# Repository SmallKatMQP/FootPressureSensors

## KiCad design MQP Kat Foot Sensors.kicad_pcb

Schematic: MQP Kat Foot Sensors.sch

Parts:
C3, C4, C5, C6, C7, C8, C9, C10, C11, C12, C13, C14, C15, C16: 100NF; C_0402_1005Metric
C17, C18: C; C_0402_1005Metric
IC1, IC2, IC3, IC4, IC5, IC6, IC7: BMP280; 8-PIN-METAL-LID-LGA_1; Manufacturer_Part_Number BMP280
J1: Conn_01x06_Male; Molex_CLIK-Mate_502443-0670_1x06-1MP_P2.00mm_Vertical
J2, J3: Conn_01x04_Male; 1x4Pads
R1: 100K; R_0402_1005Metric
U1: STM32L432KBUx; QFN-32-1EP_5x5mm_P0.5mm_EP3.45x3.45mm
U2: MIC5501-3.0YM5; SOT-23-5

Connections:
+3V3: C3.2, C4.1, C5.2, C6.1, C7.2, C8.1, C9.2, C10.1, C11.2, C12.1, C13.2, C14.1, C15.2, C16.1, C18.2, IC1.6, IC1.8, IC2.6, IC2.8, IC3.6, IC3.8, IC4.6, IC4.8, IC5.6, IC5.8, IC6.6, IC6.8, IC7.6, IC7.8, J2.4, J3.4, U1.1, U1.5, U1.17, U2.5 (VOUT)
+BATT: C17.2, J1.6, U2.1 (VIN), U2.3 (EN)
CS: J1.1, U1.14
CS1: IC1.2, U1.6
CS2: IC4.2, U1.15
CS3: IC2.2, U1.25
CS4: IC5.2, U1.20
CS5: IC7.2, U1.18
CS6: IC3.2, U1.10
CS7: IC6.2, U1.9
GND: C3.1, C4.2, C5.1, C6.2, C7.1, C8.2, C9.1, C10.2, C11.1, C12.2, C13.1, C14.2, C15.1, C16.2, C17.1, C18.1, IC1.1, IC1.7, IC2.1, IC2.7, IC3.1, IC3.7, IC4.1, IC4.7, IC5.1, IC5.7, IC6.1, IC6.7, IC7.1, IC7.7, J1.5, J2.3, J3.3, R1.2, U1.16, U1.32, U1.33, U2.2 (GND)
MISO: IC3.5, IC4.5, IC6.5, IC7.5, J1.3, U1.12
MISO2: IC1.5, IC2.5, IC5.5, U1.27
MOSI: IC3.3, IC4.3, IC6.3, IC7.3, J1.2, U1.13
MOSI2: IC1.3, IC2.3, IC5.3, U1.28
unnamed: R1.1, U1.31
RX: J3.1, U1.30
SCK: IC3.4, IC4.4, IC6.4, IC7.4, J1.4, U1.11
SCK2: IC1.4, IC2.4, IC5.4, U1.26
SWCLK: J2.1, U1.24
SWDIO: J2.2, U1.23
TX: J3.2, U1.19

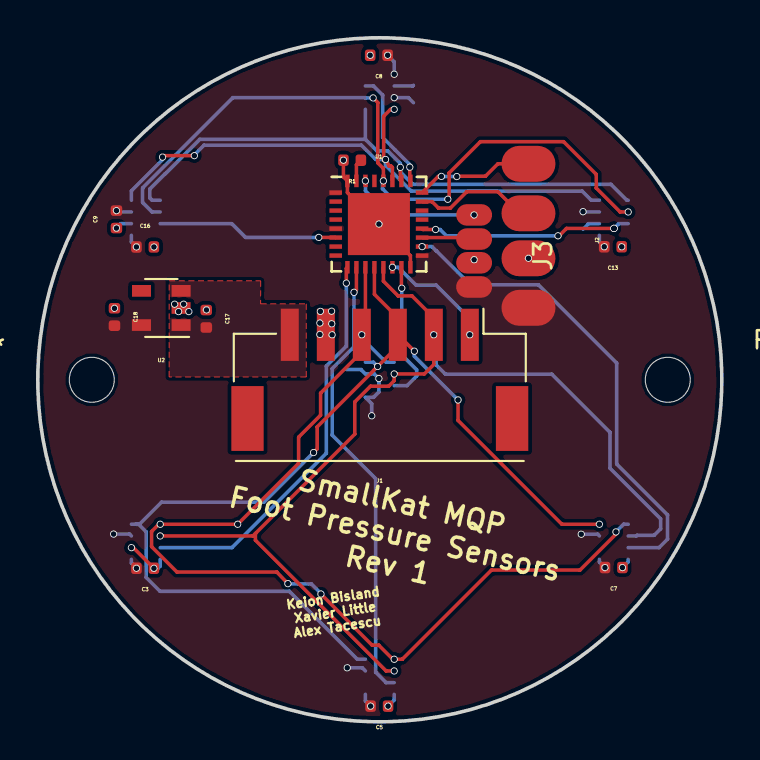
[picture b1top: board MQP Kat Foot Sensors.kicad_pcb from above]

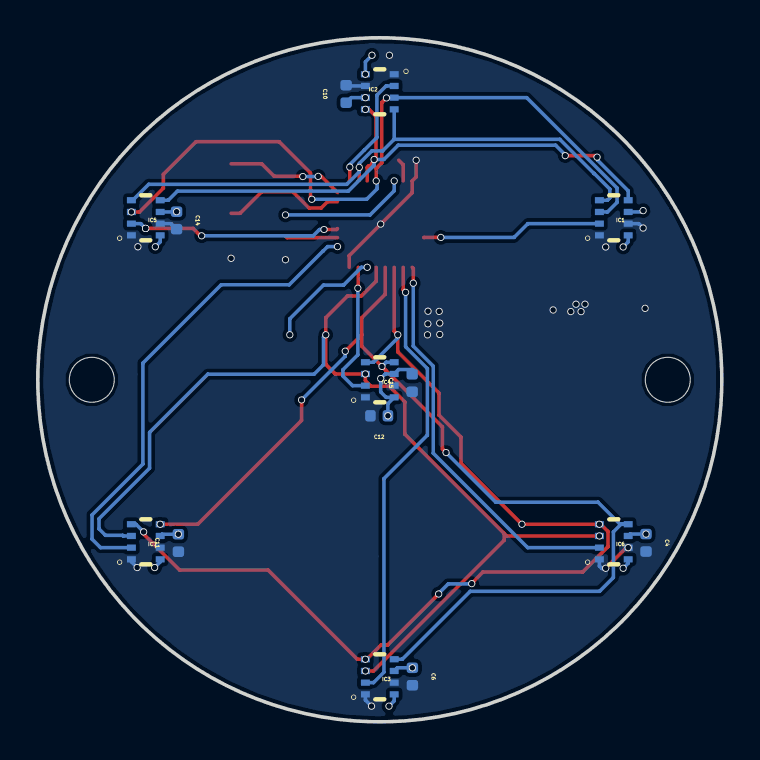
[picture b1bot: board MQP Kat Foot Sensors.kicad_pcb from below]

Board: 2 copper layers, 38.0 x 38.0 mm, 29 parts (14 on the bottom side), 22 nets.

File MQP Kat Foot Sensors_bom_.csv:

Component,Description,Part,References,Value,Footprint,Quantity Per PCB,Datasheet,Manufacturer_Name,Arrow Part Number,Arrow Price/Stock,Manufacturer_Part_Number
1,Unpolarized capacitor,C,C3 C4 C5 C6 C7 C8 C9 C10 C11 C12 C13 C14 C15 C16,100NF,C_0402_1005Metric,14,~,,,,
2,Unpolarized capacitor,C,C1 C2,10PF,C_0402_1005Metric,2,~,,,,
3,Unpolarized capacitor,C,C17 C18,C,C_0402_1005Metric,2,~,,,,
4,Digital Pressure Sensor,BMP280,IC1 IC2 IC3 IC4 IC5 IC6 IC7,BMP280,8-PIN-METAL-LID-LGA_1,7,https://ae-bst.resource.bosch.com/media/_tech/media/datashee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,Bosch,BMP280,https://www.arrow.com/en/products/bmp280/bosch,BMP280
5,"Generic connector, single row, 01x04, script generated (kicad-library-utils/schlib/autogen/connector/)",Conn_01x04_Male,J2,Conn_01x04_Male,1x4Pads,1,~,,,,
6,"Generic connector, single row, 01x06, script generated (kicad-library-utils/schlib/autogen/connector/)",Conn_01x06_Male,J1,Conn_01x06_Male,Molex_CLIK-Mate_502443-0670_1x06-1MP_P2.00mm_Vertical,1,~,,,,
7,Resistor,R,R1,100K,R_0402_1005Metric,1,~,,,,
8,"300mA Low-dropout Voltage Regulator, Vout 3.0V, Vin up to 5.5V, SOT-23",MIC5501-3.0YM5,U2,MIC5501-3.0YM5,SOT-23-5,1,http://ww1.microchip.com/downloads/en/DeviceDoc/MIC550X.pdf,,,,
9,"ARM Cortex-M4 MCU, 128KB flash, 64KB RAM, 80MHz, 1.71-3.6V, 26 GPIO, UFQFPN-32",STM32L432KBUx,U1,STM32L432KBUx,QFN-32-1EP_5x5mm_P0.5mm_EP3.45x3.45mm,1,http://www.st.com/st-web-ui/static/active/en/resource/techni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,,,,
10,"Four pin crystal (GND on pins 2 and 4), e.g. in SMD package",Crystal_GND24,Y1,Crystal_GND24,Crystal_SMD_2016-4Pin_2.0x1.6mm,1,~,,,,





Component Groups:,10
Component Count:,31
Fitted Components:,31
Number of PCBs:,1
Total components:,31
Schematic Version:,
Schematic Date:,
BoM Date:,Sun 26 Aug 2018 05:51:56 PM EDT
Schematic Source:,/home/kbisland/Documents/MQP Kat Foot Sensors/MQP Kat Foot Sensors.sch
KiCad Version:,Eeschema 5.0.0-fee4fd1~66~ubuntu16.04.1

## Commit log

2018-08-27 Added all files for v1
2018-10-24 updated pinout
